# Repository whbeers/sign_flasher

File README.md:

# Transistor-driven 555 LED flasher

This is a simple LED driver circuit using two 555s and a pair of NPN/PNP transistors to drive several LEDs meant to outline a small sign. Designed with my son for a St Patrick's Day project, in [KiCAD](https://www.kicad.org). 

[Schematic PDF](schematics/sign_flasher-latest.pdf)

## Credit
The underlying circuit is based on [a 555 schematic](https://mechatrofice.com/circuits/555/led-flasher-circuit) I found when searching for circuits that would fulfill the design requirements given to me by my son.

Trimpot symbol, footprint, and 3D model courtesy of [SnapEDA](https://www.snapeda.com/parts/3306F-1-103/Bourns/view-part/). ([Additional license details](hardware/SnapEDA_Licensing.txt))

*I am not affiliated with any of the brands, sites, or products named in this overview.*

## Versioning

My pcb designs utilize the following versioning scheme (I'll add to this as I produce more revisions):
 - v0.0XX: A candidate design that has not yet been produced and tested.
 - v0.XX: A design that has been produced, tested, and any initial errors addressed.

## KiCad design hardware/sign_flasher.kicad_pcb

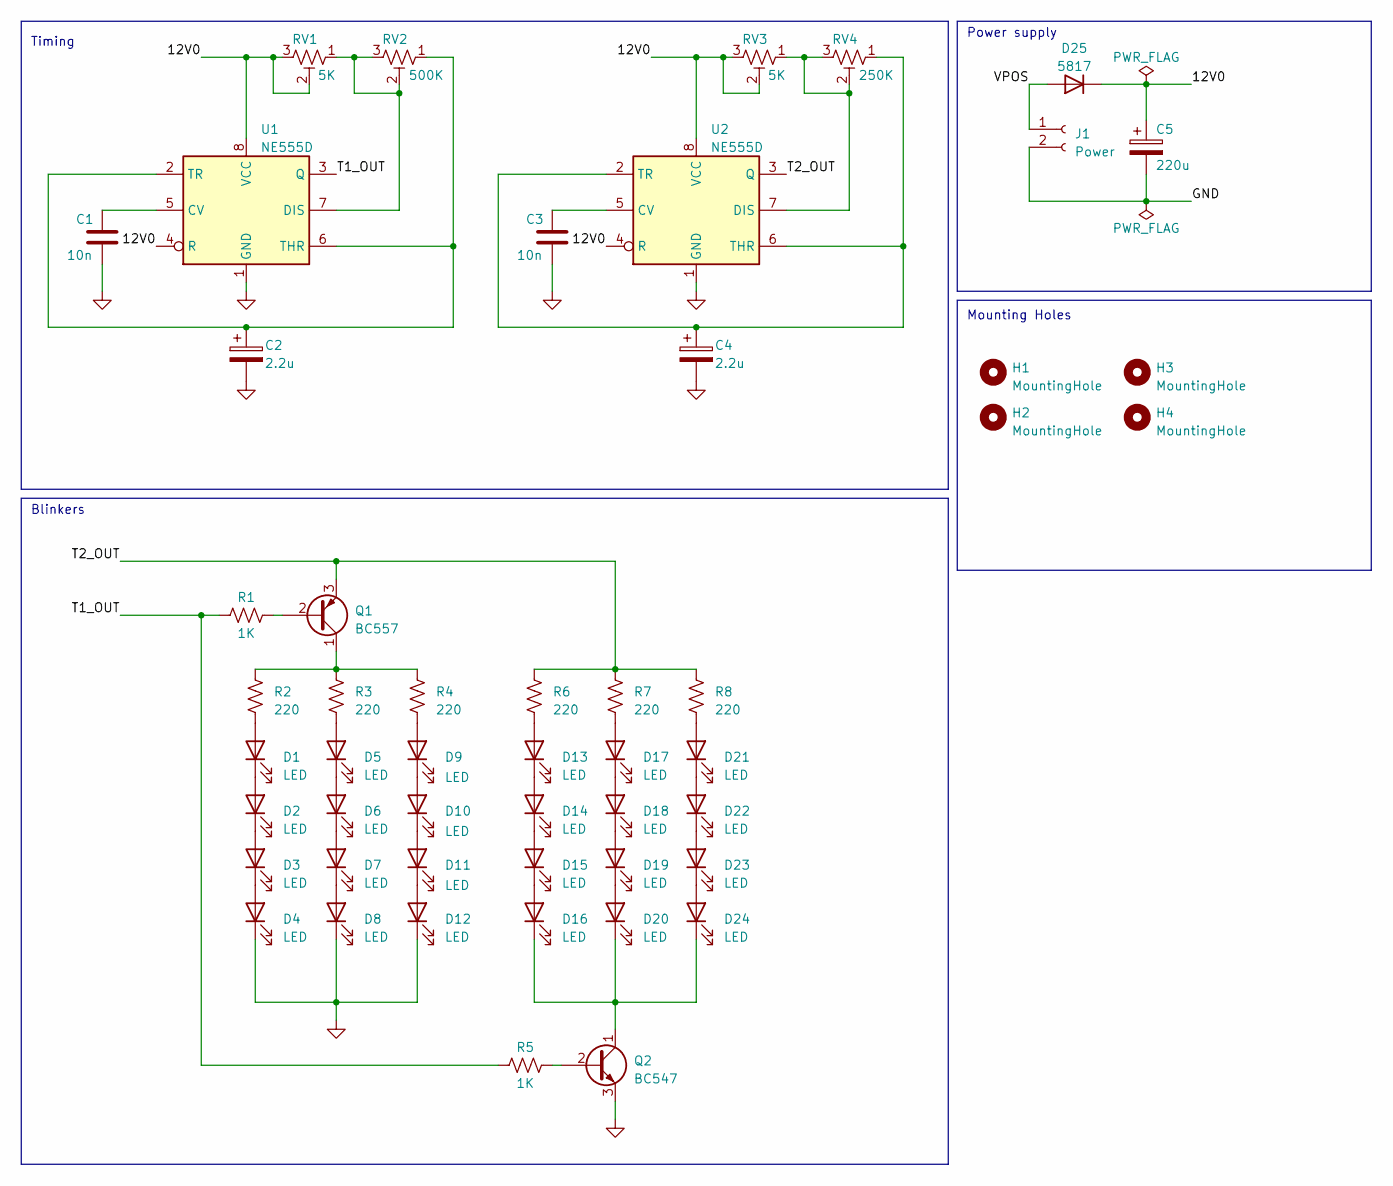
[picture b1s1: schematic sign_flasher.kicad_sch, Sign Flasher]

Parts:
C1, C3: 10n; C_Rect_L7.2mm_W2.5mm_P5.00mm_FKS2_FKP2_MKS2_MKP2
C2, C4: 2.2u; CP_Radial_D4.0mm_P2.00mm
C5: 220u; CP_Radial_D6.3mm_P2.50mm
D1, D2, D3, D4, D5, D6, D7, D8, D9, D10, D11, D12, D13, D14, D15, D16, D17, D18, D19, D20, D21, D22, D23, D24: LED; LED_D5.0mm
D25: 5817; D_DO-41_SOD81_P7.62mm_Horizontal
H1, H2, H3, H4: MountingHole; MountingHole_4mm_Pad
J1: Power; JST_XH_B2B-XH-A_1x02_P2.50mm_Vertical
Q1: BC557; TO-92
Q2: BC547; TO-92
R1, R5: 1K; R_Axial_DIN0207_L6.3mm_D2.5mm_P7.62mm_Horizontal
R2, R3, R4, R6, R7, R8: 220; R_Axial_DIN0207_L6.3mm_D2.5mm_P7.62mm_Horizontal
RV1, RV3: 5K; TRIM_3306F-1-103
RV2: 500K; TRIM_3306F-1-103
RV4: 250K; TRIM_3306F-1-103
U1, U2: NE555D; DIP-8_W7.62mm

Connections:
/12V0: C5.1, D25.1 (K), RV1.2, RV1.3, RV3.2, RV3.3, U1.4 (R), U1.8 (VCC), U2.4 (R), U2.8 (VCC)
/T1_OUT: R1.1, R5.1, U1.3 (Q)
/T2_OUT: Q1.3 (E), R6.1, R7.1, R8.1, U2.3 (Q)
/VPOS: D25.2 (A), J1.1
GND: C1.2, C2.2, C3.2, C4.2, C5.2, D4.1 (K), D8.1 (K), D12.1 (K), J1.2, Q2.3 (E), U1.1 (GND), U2.1 (GND)
unnamed: D1.2 (A), R2.2
unnamed: D1.1 (K), D2.2 (A)
unnamed: D2.1 (K), D3.2 (A)
unnamed: D3.1 (K), D4.2 (A)
unnamed: D5.2 (A), R3.2
unnamed: D5.1 (K), D6.2 (A)
unnamed: D6.1 (K), D7.2 (A)
unnamed: D7.1 (K), D8.2 (A)
unnamed: D9.2 (A), R4.2
unnamed: D9.1 (K), D10.2 (A)
unnamed: D10.1 (K), D11.2 (A)
unnamed: D11.1 (K), D12.2 (A)
unnamed: D13.2 (A), R6.2
unnamed: D13.1 (K), D14.2 (A)
unnamed: D14.1 (K), D15.2 (A)
unnamed: D15.1 (K), D16.2 (A)
unnamed: D16.1 (K), D20.1 (K), D24.1 (K), Q2.1 (C)
unnamed: D17.2 (A), R7.2
unnamed: D17.1 (K), D18.2 (A)
unnamed: D18.1 (K), D19.2 (A)
unnamed: D19.1 (K), D20.2 (A)
unnamed: D21.2 (A), R8.2
unnamed: D21.1 (K), D22.2 (A)
unnamed: D22.1 (K), D23.2 (A)
unnamed: D23.1 (K), D24.2 (A)
unnamed: Q1.2 (B), R1.2
unnamed: Q1.1 (C), R2.1, R3.1, R4.1
unnamed: Q2.2 (B), R5.2
unnamed: C1.1, U1.5 (CV)
unnamed: RV1.1, RV2.2, RV2.3, U1.7 (DIS)
unnamed: C2.1, RV2.1, U1.2 (TR), U1.6 (THR)
unnamed: C3.1, U2.5 (CV)
unnamed: RV3.1, RV4.2, RV4.3, U2.7 (DIS)
unnamed: C4.1, RV4.1, U2.2 (TR), U2.6 (THR)

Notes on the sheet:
Blinkers
Mounting Holes
Timing
Power supply

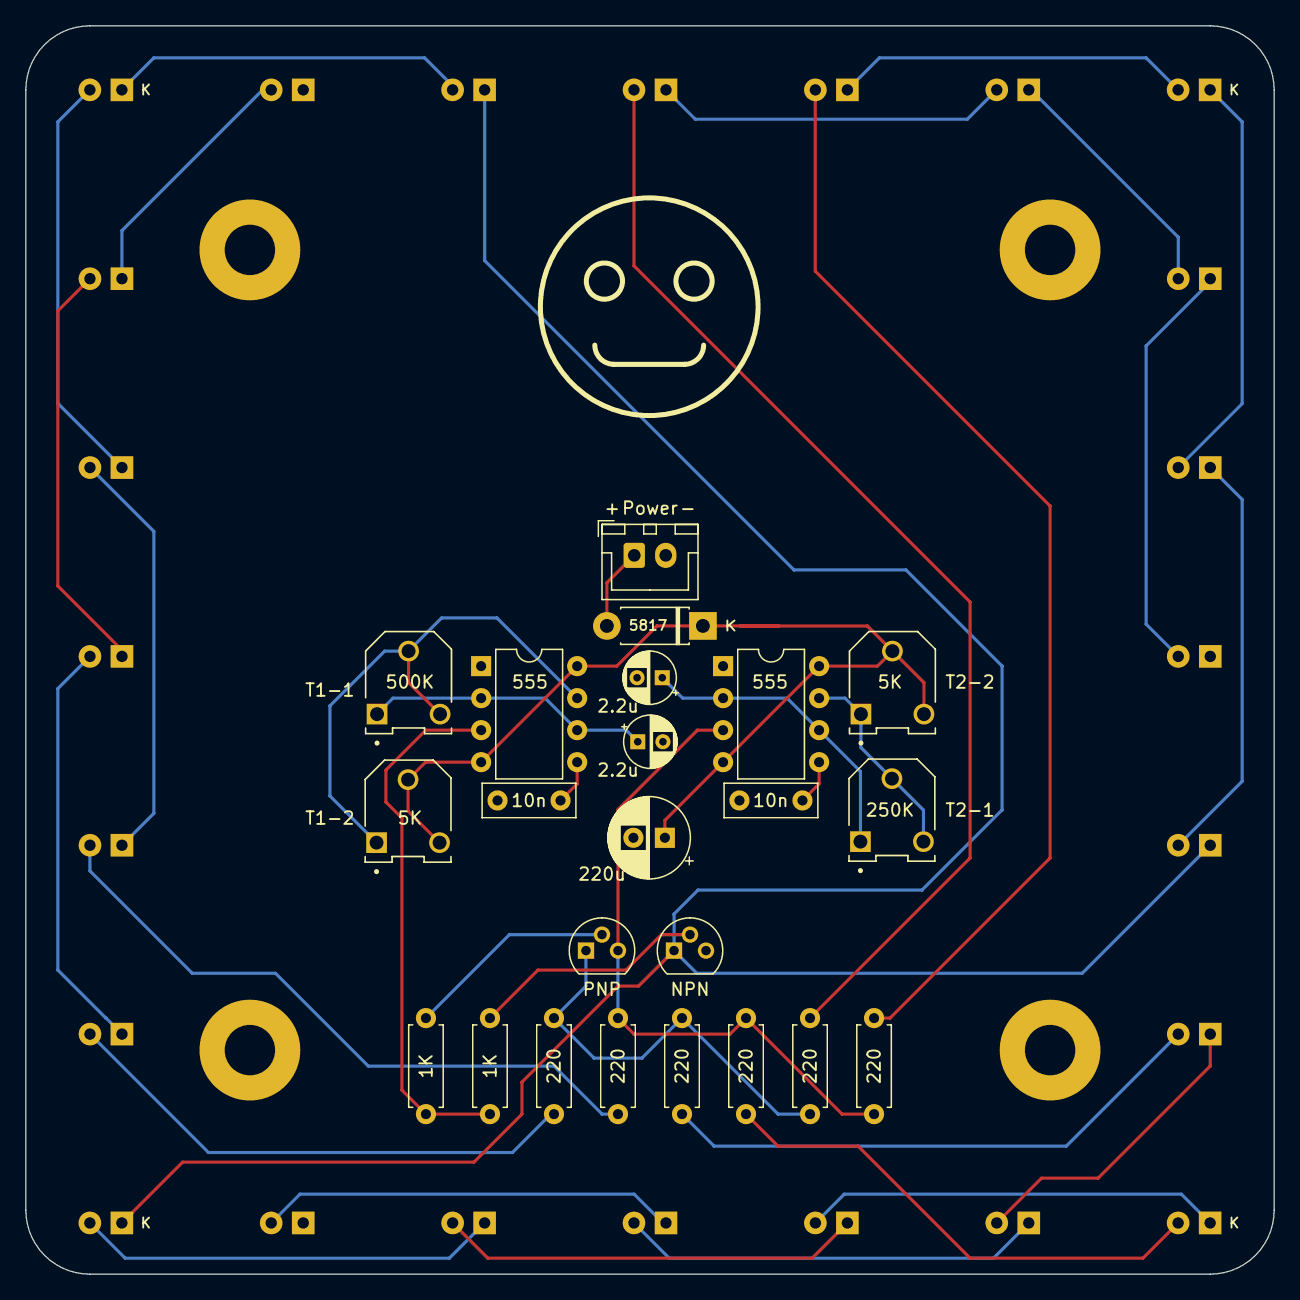
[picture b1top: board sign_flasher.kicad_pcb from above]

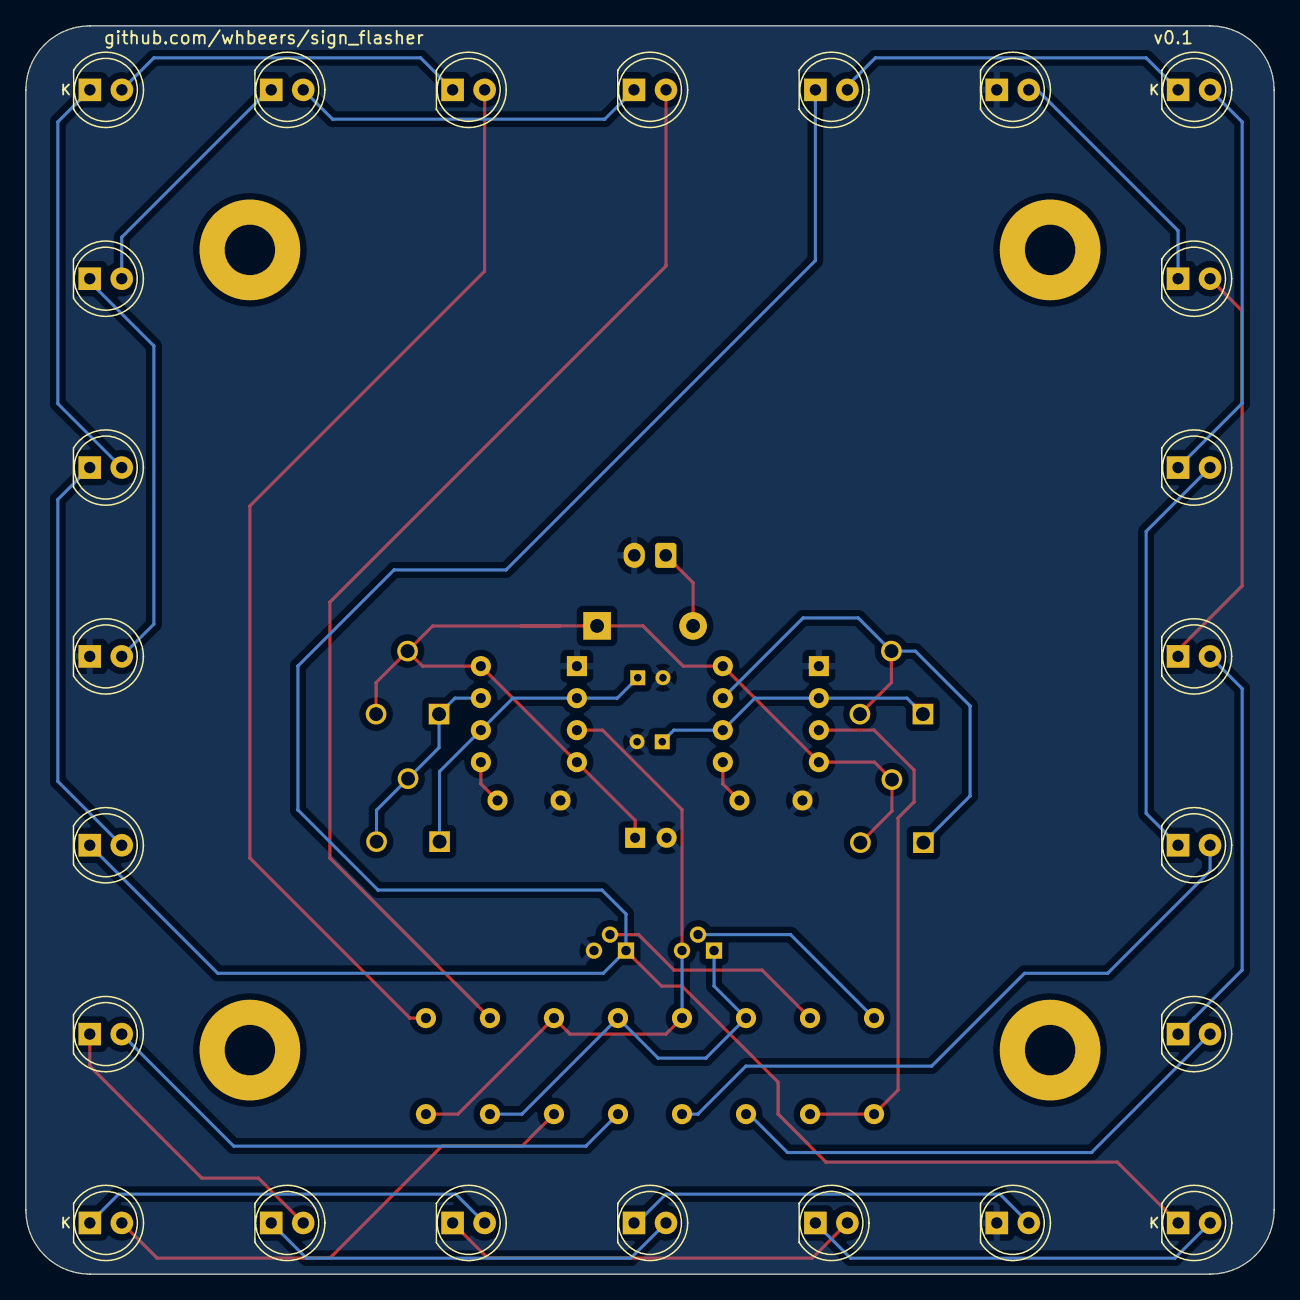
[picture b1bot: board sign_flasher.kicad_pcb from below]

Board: 2 copper layers, 99.1 x 99.1 mm, 51 parts (24 on the bottom side), 39 nets.

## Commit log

2023-03-10 README.md
2023-03-10 schematic plots and update to schematic script
2023-03-10 fix schematic links
2023-03-10 finished design and layout with TODOs
2023-03-10 get under 100mmsq, add mounting holes
2023-03-10 generate new schematic (although nothing should have updated)
2023-03-11 add explicit note about SnapEDA trimpot models
2023-03-11 correct readme
2023-03-11 more corrections
2023-03-13 Update to latest stable kicad version:
    - fixed issue rendering certain 3d models in color
    - had to fix some text rendering changes
2023-03-16 Address issues identified with rev v0.01:
    - Revise schematic to indicate the need for 12V power
    - Add reverse voltage protection diode
2023-03-16 adjust position of replaced capacitor footprint
2023-03-27 update readme and rename snapeda licensing file
